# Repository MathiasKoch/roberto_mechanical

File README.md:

# Roberto the robot! Mechanical repository containing PCBs and mechanical drawing files.

Please see the roberto_robot repository for the actual robot software, issue tracker and wiki

https://github.com/smilykoch/roberto_robot

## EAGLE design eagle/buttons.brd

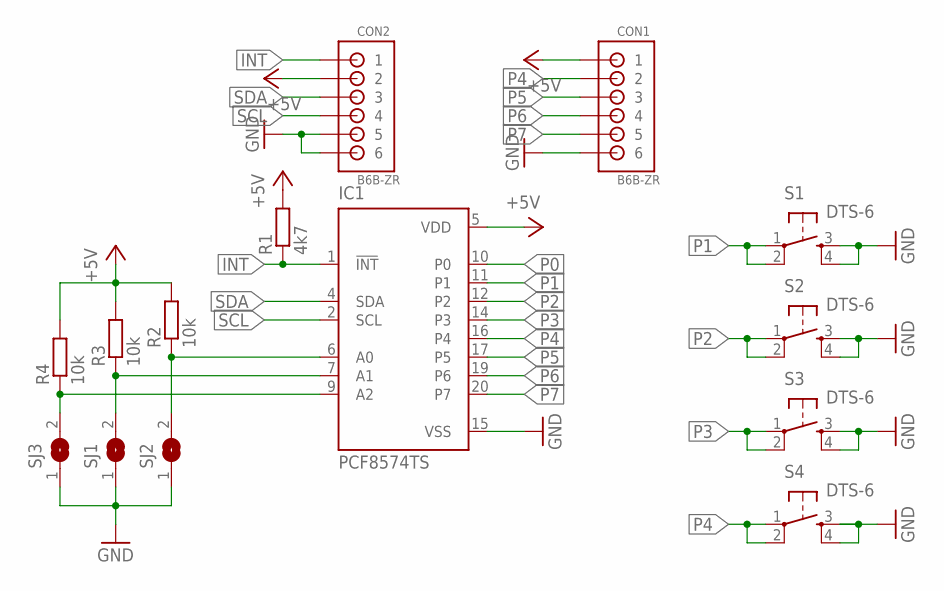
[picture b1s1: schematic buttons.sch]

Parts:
CON1, CON2: B6B-ZR
IC1: PCF8574TS; SSOP20
R1: 4k7; R0805
R2, R3, R4: 10k; R0805
S1, S2, S3, S4: DTS-6
SJ1, SJ2, SJ3: SJ

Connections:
+5V: CON1.1, CON2.2, IC1.5 (VDD), R1.2, R2.2, R3.2, R4.2
GND: CON1.6, CON2.5, CON2.6, IC1.15 (VSS), S1.3, S1.4, S2.3, S2.4, S3.3, S3.4, S4.3, S4.4, SJ1.1, SJ2.1, SJ3.1
INT: CON2.1, IC1.1 (!INT), R1.1
unnamed: IC1.6 (A0), R2.1, SJ2.2
unnamed: IC1.7 (A1), R3.1, SJ1.2
unnamed: IC1.9 (A2), R4.1, SJ3.2
P0: IC1.10 (P0)
P1: IC1.11 (P1), S1.1, S1.2
P2: IC1.12 (P2), S2.1, S2.2
P3: IC1.14 (P3), S3.1, S3.2
P4: CON1.2, IC1.16 (P4), S4.1, S4.2
P5: CON1.3, IC1.17 (P5)
P6: CON1.4, IC1.19 (P6)
P7: CON1.5, IC1.20 (P7)
SCL: CON2.4, IC1.2 (SCL)
SDA: CON2.3, IC1.4 (SDA)

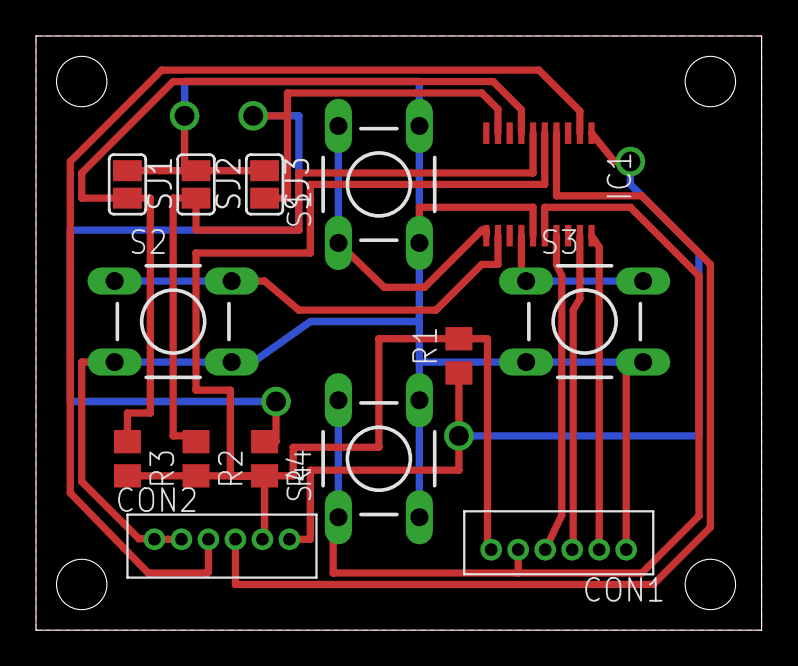
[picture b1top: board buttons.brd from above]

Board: 2 copper layers, 40.3 x 33.0 mm, 14 parts (0 on the bottom side), 15 nets.

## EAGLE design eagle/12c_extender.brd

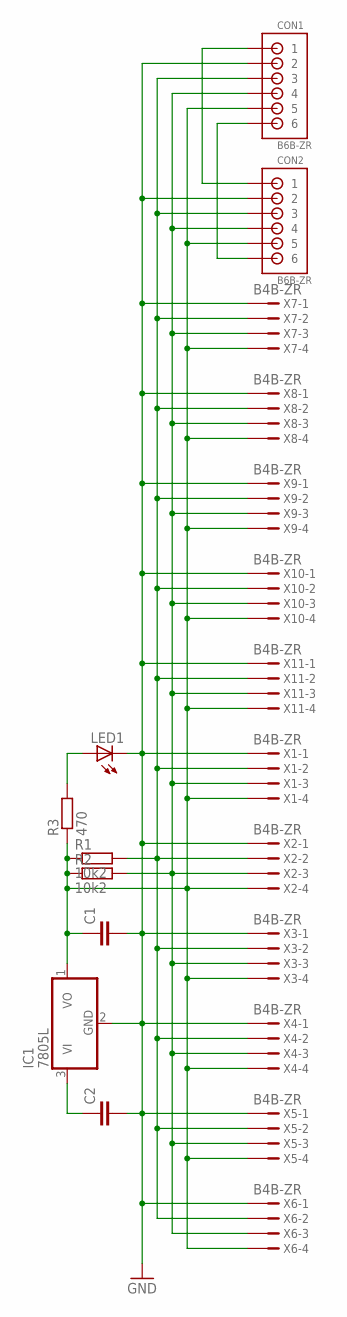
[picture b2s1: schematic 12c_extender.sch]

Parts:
C1, C2: C-EUC0805; C0805
CON1, CON2: B6B-ZR
IC1: 7805L; TO92
LED1: LEDSMT1206; 1206
R1, R2: 10k2; R0805
R3: 470; R0805
X1, X2, X3, X4, X5, X6, X7, X8, X9, X10, X11: B4B-ZR

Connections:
+5V: C1.1, CON1.5, CON2.5, IC1.1 (VO), R1.1, R2.1, R3.1, X1.4, X2.4, X3.4, X4.4, X5.4, X6.4, X7.4, X8.4, X9.4, X10.4, X11.4
GND: C1.2, C2.2, CON1.2, CON2.2, IC1.2 (GND), LED1.C, X1.1, X2.1, X3.1, X4.1, X5.1, X6.1, X7.1, X8.1, X9.1, X10.1, X11.1
unnamed: C2.1, IC1.3 (VI)
unnamed: LED1.A, R3.2
unnamed: CON1.1, CON2.1
unnamed: CON1.6, CON2.6
SCL: CON1.4, CON2.4, R2.2, X1.3, X2.3, X3.3, X4.3, X5.3, X6.3, X7.3, X8.3, X9.3, X10.3, X11.3
SDA: CON1.3, CON2.3, R1.2, X1.2, X2.2, X3.2, X4.2, X5.2, X6.2, X7.2, X8.2, X9.2, X10.2, X11.2

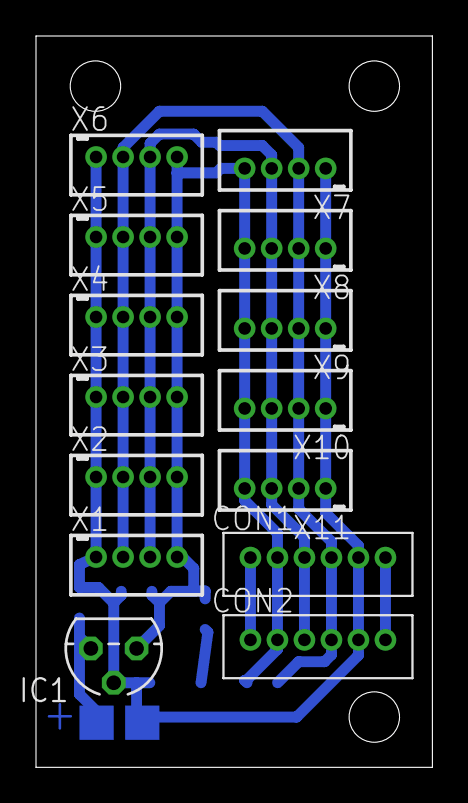
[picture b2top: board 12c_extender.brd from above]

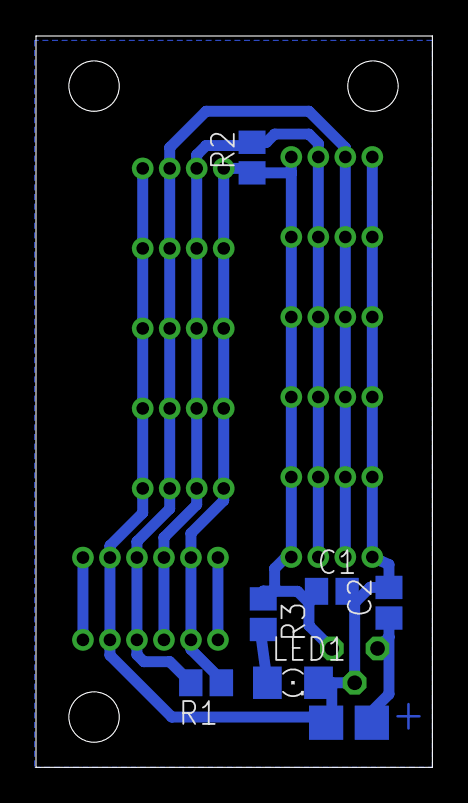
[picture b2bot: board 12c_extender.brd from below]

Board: 2 copper layers, 22.0 x 40.6 mm, 20 parts (6 on the bottom side), 8 nets.

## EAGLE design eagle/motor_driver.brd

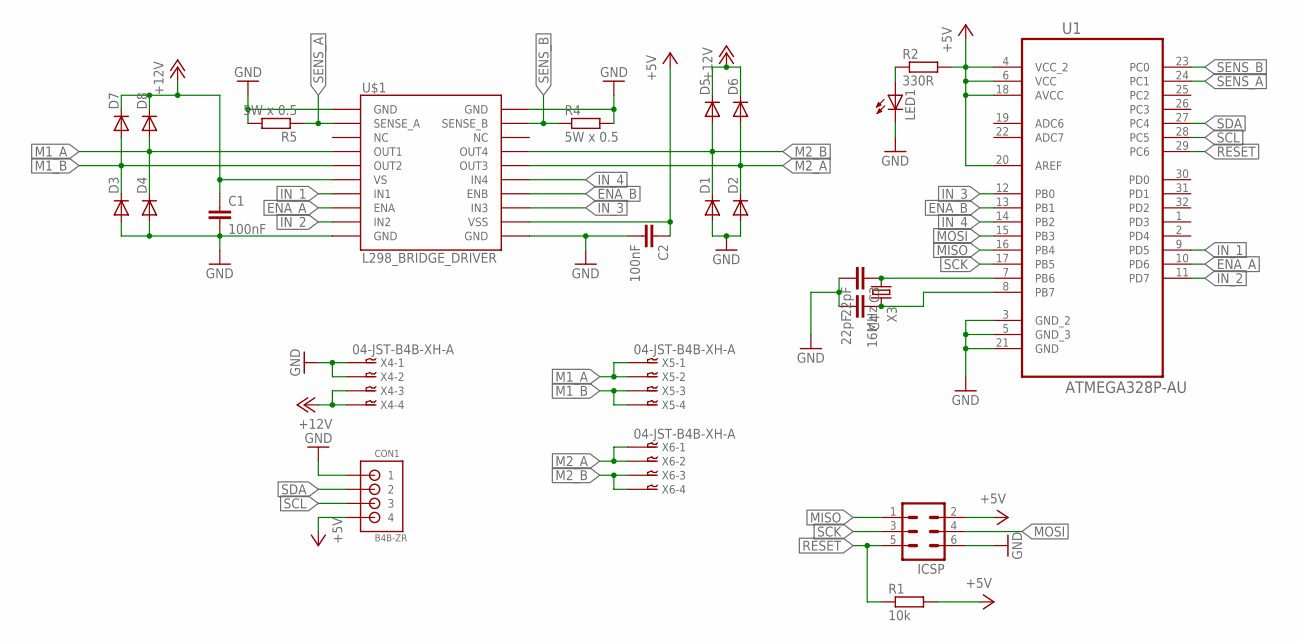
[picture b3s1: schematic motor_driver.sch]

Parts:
C1, C2: 100nF; C1206K
C3, C4: 22pF; C1206K
CON1: B4B-ZR
D1, D2, D3, D4, D5, D6, D7, D8: DIODE-SMC; SMC
ICSP: MA03-2
LED1: LEDCHIPLED_1206; CHIPLED_1206
R1: 10k; M3216
R2: 330R; M3216
R4, R5: 5W x 0.5; R6332
U1: ATMEGA328P-AU; QFP80P900X900X120-32N
U$1: L298_BRIDGE_DRIVER; POWERSO20
X3: 16MHz; 7.5X5-2-PAD
X4, X5, X6: 04-JST-B4B-XH-A; B4B-XH

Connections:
+5V: C2.1, CON1.4, ICSP.2, R1.2, R2.2, U1.4 (VCC_2), U1.6 (VCC), U1.18 (AVCC), U1.20 (AREF), U$1.12 (VSS)
+12V: C1.1, D5.C, D6.C, D7.C, D8.C, U$1.6 (VS), X4.P$3
ENA_A: U1.10 (PD6), U$1.8 (ENA)
ENA_B: U1.13 (PB1), U$1.14 (ENB)
GND: C1.2, C2.2, C3.2, C4.2, CON1.1, D1.A, D2.A, D3.A, D4.A, ICSP.6, LED1.C, R4.P$2 (2), R5.P$2 (2), U1.3 (GND_2), U1.5 (GND_3), U1.21 (GND), U$1.1 (GND), U$1.10 (GND), U$1.11 (GND), U$1.20 (GND), X4.P$2
IN_1: U1.9 (PD5), U$1.7 (IN1)
IN_2: U1.11 (PD7), U$1.9 (IN2)
IN_3: U1.12 (PB0), U$1.13 (IN3)
IN_4: U1.14 (PB2), U$1.15 (IN4)
M1_A: D4.C, D8.A, U$1.4 (OUT1), X5.P$1, X5.P$2
M1_B: D3.C, D7.A, U$1.5 (OUT2), X5.P$3, X5.P$4
M2_A: D2.C, D6.A, U$1.16 (OUT3), X6.P$1, X6.P$2
M2_B: D1.C, D5.A, U$1.17 (OUT4), X6.P$3, X6.P$4
MISO: ICSP.1, U1.16 (PB4)
MOSI: ICSP.4, U1.15 (PB3)
unnamed: LED1.A, R2.1
unnamed: C4.1, U1.8 (PB7), X3.2
unnamed: C3.1, U1.7 (PB6), X3.1
RESET: ICSP.5, R1.1, U1.29 (PC6)
SCK: ICSP.3, U1.17 (PB5)
SCL: CON1.3, U1.28 (PC5)
SDA: CON1.2, U1.27 (PC4)
SENS_A: R5.P$1 (1), U1.24 (PC1), U$1.2 (SENSE_A)
SENS_B: R4.P$1 (1), U1.23 (PC0), U$1.19 (SENSE_B)

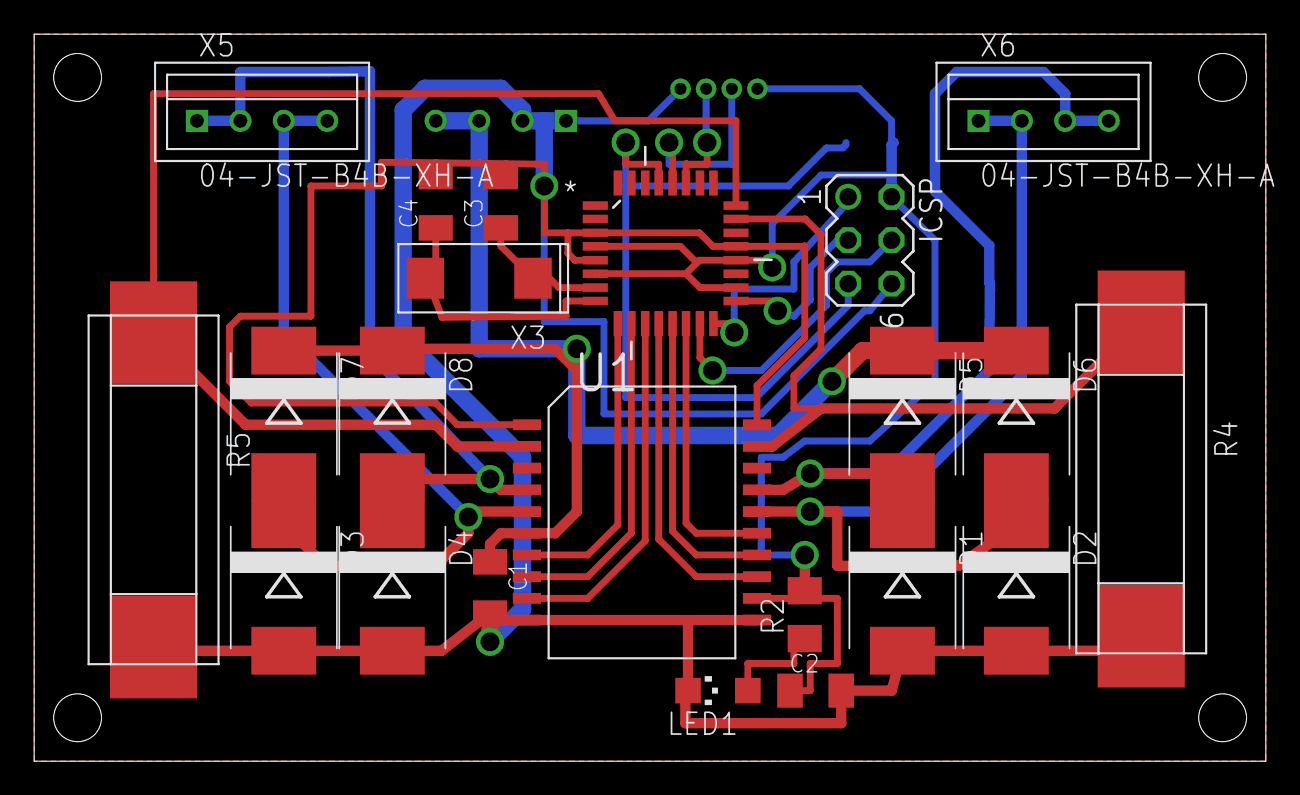
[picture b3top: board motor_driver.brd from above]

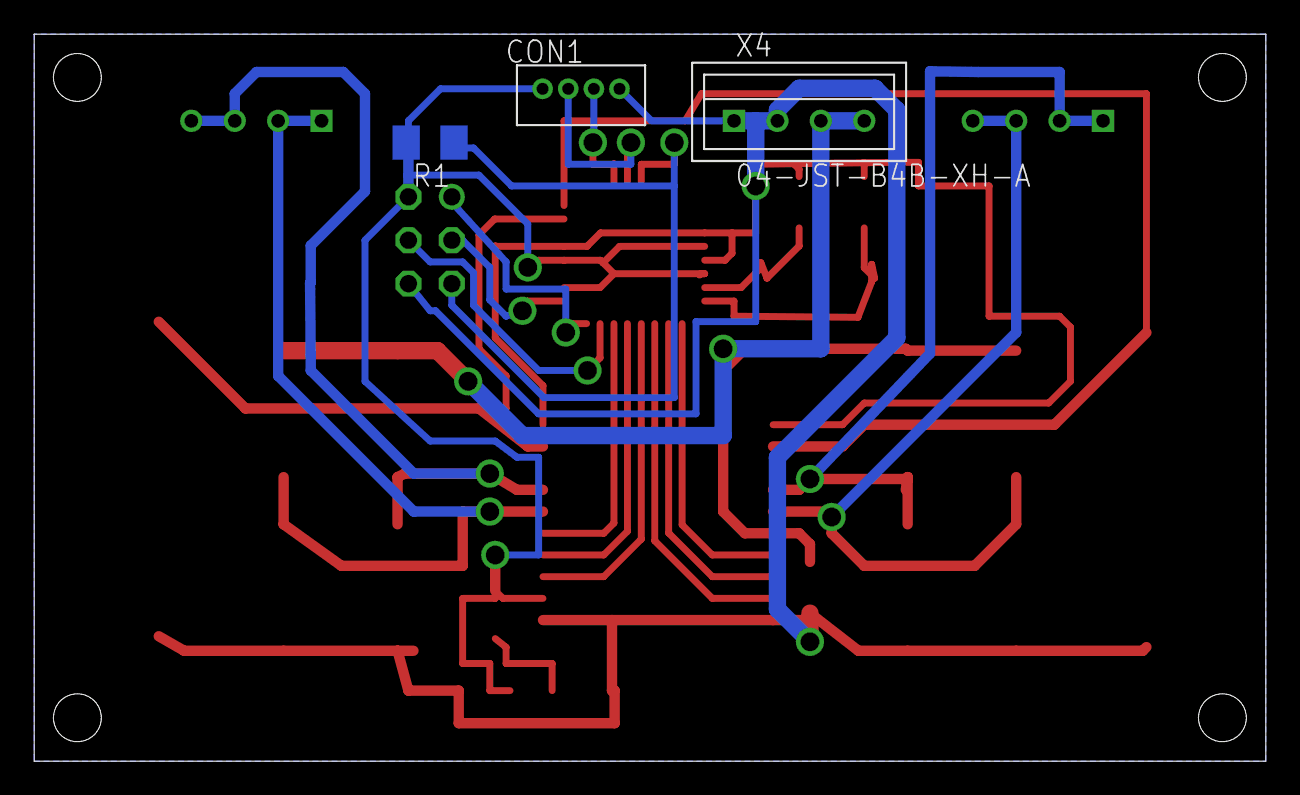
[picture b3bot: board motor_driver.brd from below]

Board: 2 copper layers, 72.1 x 42.5 mm, 25 parts (3 on the bottom side), 24 nets.

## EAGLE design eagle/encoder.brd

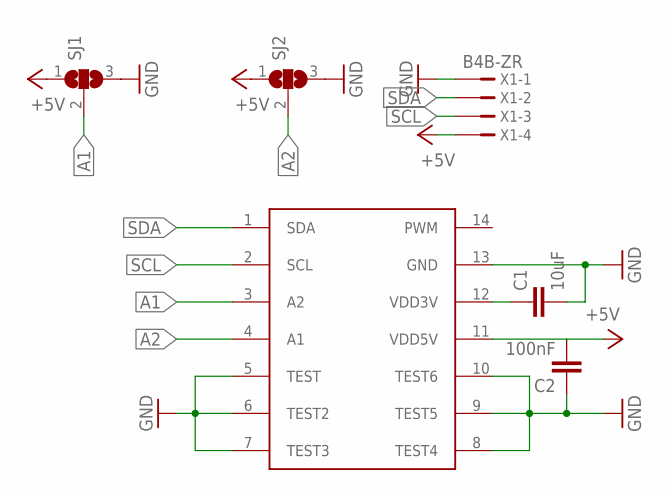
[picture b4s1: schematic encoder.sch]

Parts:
C1: 10uF; C0805K
C2: 100nF; C0805K
SJ1, SJ2: SJ2W; SJ_2
U$1: AS5048B; TSSOP14
X1: B4B-ZR

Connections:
+5V: C2.2, SJ1.1, SJ2.1, U$1.11 (VDD5V), X1.4
A1: SJ1.2, U$1.3 (A2)
A2: SJ2.2, U$1.4 (A1)
GND: C1.2, C2.1, SJ1.3, SJ2.3, U$1.5 (TEST), U$1.6 (TEST2), U$1.7 (TEST3), U$1.8 (TEST4), U$1.9 (TEST5), U$1.10 (TEST6), U$1.13 (GND), X1.1
unnamed: C1.1, U$1.12 (VDD3V)
SCL: U$1.2 (SCL), X1.3
SDA: U$1.1 (SDA), X1.2

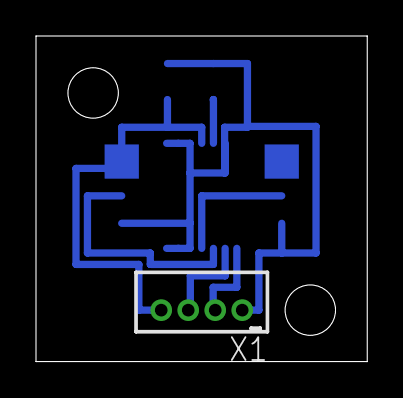
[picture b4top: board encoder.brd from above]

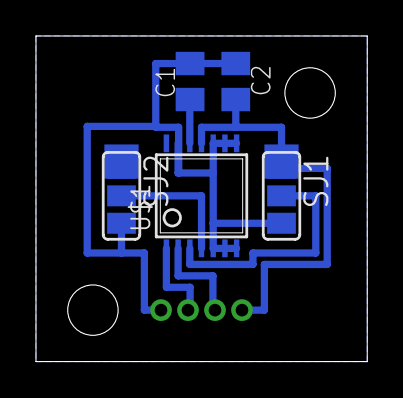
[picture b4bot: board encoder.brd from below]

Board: 2 copper layers, 18.4 x 18.1 mm, 6 parts (5 on the bottom side), 7 nets.

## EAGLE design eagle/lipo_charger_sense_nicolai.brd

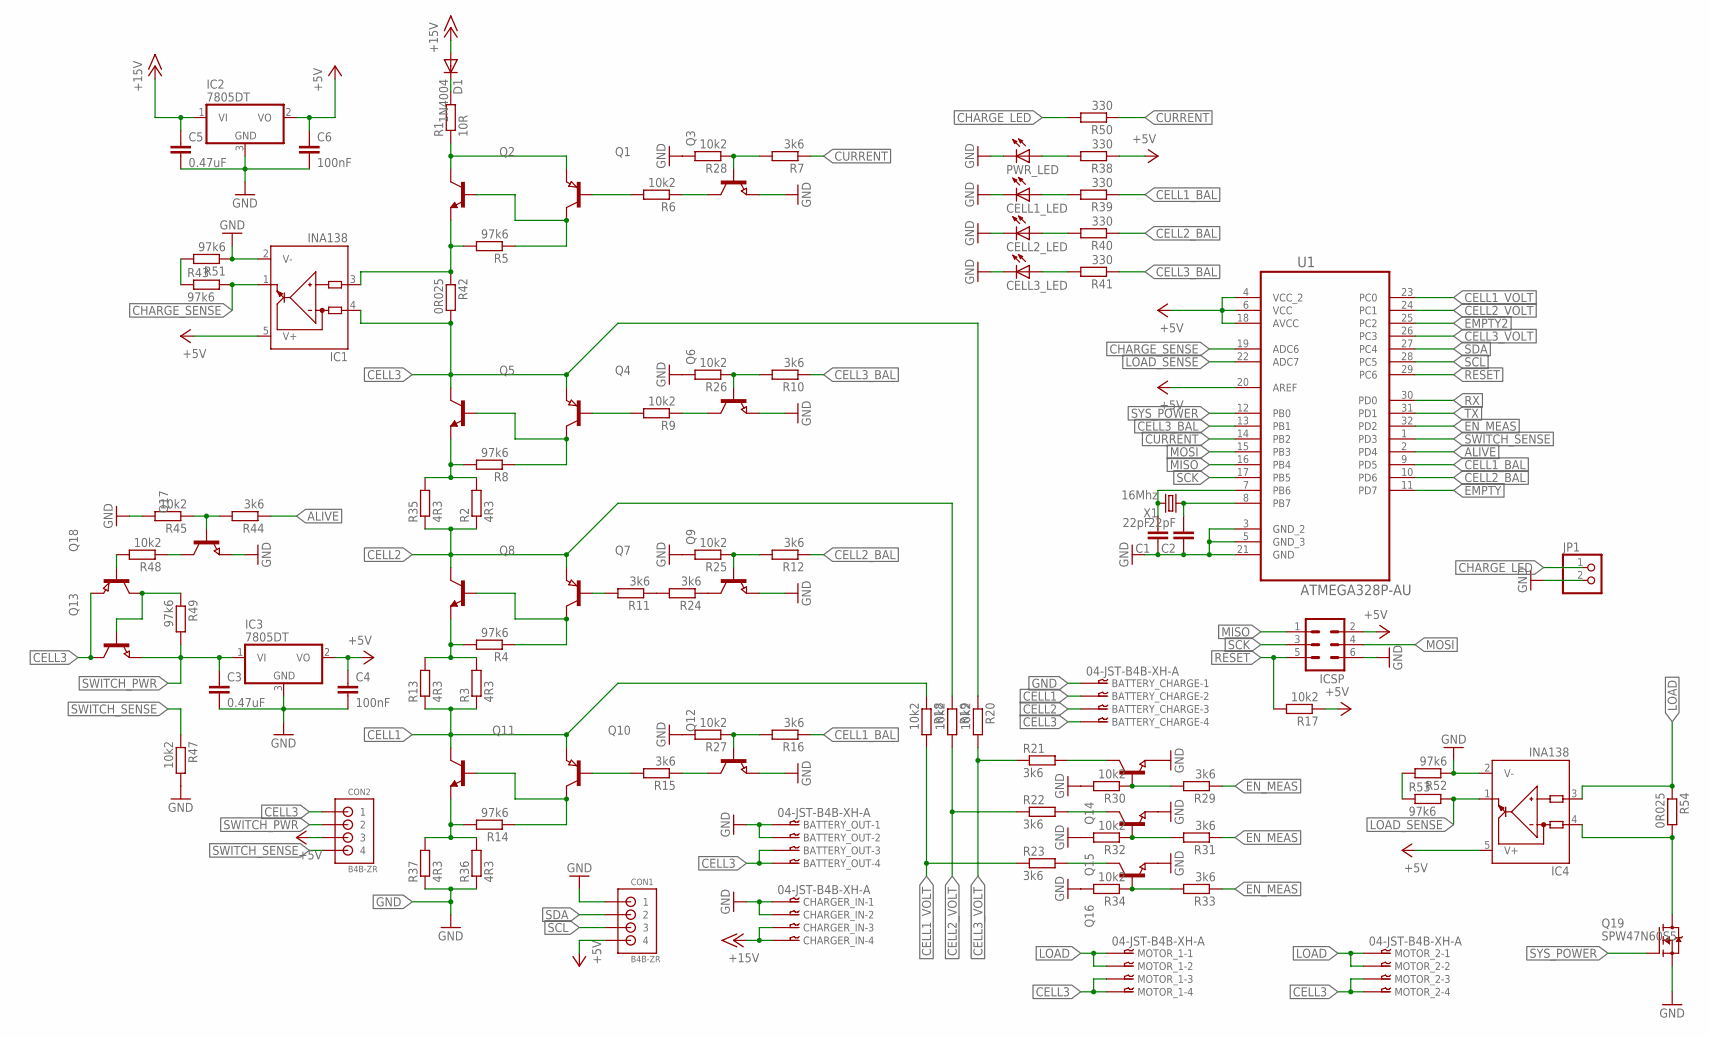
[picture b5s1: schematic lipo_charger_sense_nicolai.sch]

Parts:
BATTERY_CHARGE: 04-JST-B4B-XH-A; B4B-XH
BATTERY_OUT: 04-JST-B4B-XH-A; B4B-XH
C1, C2: 22pF; C0805K
C3, C5: 0.47uF; C0805K
C4, C6: 100nF; C0805K
CELL1_LED, CELL2_LED, CELL3_LED: LEDSMT1206; 1206
CHARGER_IN: 04-JST-B4B-XH-A; B4B-XH
CON1, CON2: B4B-ZR
D1: 1N4004; DO41-10
IC1, IC4: INA138; SOT23-5
IC2, IC3: 7805DT; TO252
ICSP: MA03-2
JP1: PINHD-1X2/90; 1X02/90
MOTOR_1, MOTOR_2: 04-JST-B4B-XH-A; B4B-XH
PWR_LED: LEDSMT1206; 1206
Q1, Q4, Q7, Q10, Q18: PNP-TRANSISTOR_SOT23; SOT23
Q2, Q5, Q8, Q11: -NPN-; DPAK
Q3, Q6, Q9, Q12, Q13, Q14, Q15, Q16, Q17: NPN-TRANSISTOR_SOT23; SOT23
Q19: SPW47N60S5; DPACK_2
R1: 10R; SMW5
R2, R3, R13, R35, R36, R37: 4R3; SMW5
R4, R5, R8, R14, R43, R49, R51, R52, R53: 97k6; R0805
R6, R9, R17, R18, R19, R20, R25, R26, R27, R28, R30, R32, R34, R45, R47, R48: 10k2; R0805
R7, R10, R11, R12, R15, R16, R21, R22, R23, R24, R29, R31, R33, R44: 3k6; R0805
R38, R39, R40, R41, R50: 330; R0805
R42, R54: 0R025; R2512
U1: ATMEGA328P-AU; QFP80P900X900X120-32N
X1: 16Mhz; 7.5X5-2-PAD

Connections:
+5V: C4.1, C6.1, CON1.4, CON2.3, IC1.5 (V+), IC2.2 (VO), IC3.2 (VO), IC4.5 (V+), ICSP.2, R17.1, R38.1, U1.4 (VCC_2), U1.6 (VCC), U1.18 (AVCC), U1.20 (AREF)
+15V: C5.1, CHARGER_IN.P$3, CHARGER_IN.P$4, D1.A, IC2.1 (VI)
ALIVE: R44.1, U1.2 (PD4)
CELL1: BATTERY_CHARGE.P$2, Q10.2 (E), Q11.3 (C), R3.P$1 (1), R13.P$1 (1), R18.1
CELL1_BAL: R16.1, R39.1, U1.9 (PD5)
CELL1_VOLT: R18.2, R23.1, U1.23 (PC0)
CELL2: BATTERY_CHARGE.P$3, Q7.2 (E), Q8.3 (C), R2.P$1 (1), R19.1, R35.P$1 (1)
CELL2_BAL: R12.1, R40.1, U1.10 (PD6)
CELL2_VOLT: R19.2, R22.1, U1.24 (PC1)
CELL3: BATTERY_CHARGE.P$4, BATTERY_OUT.P$3, BATTERY_OUT.P$4, CON2.1, IC1.4 (IN-), MOTOR_1.P$3, MOTOR_1.P$4, MOTOR_2.P$3, MOTOR_2.P$4, Q4.2 (E), Q5.3 (C), Q13.3 (C), Q18.2 (E), R20.1, R42.2
CELL3_BAL: R10.1, R41.1, U1.13 (PB1)
CELL3_VOLT: R20.2, R21.1, U1.26 (PC3)
CELL5: IC4.4 (IN-), Q19.D, R54.2
CHARGE_LED: JP1.1, R50.2
CHARGE_SENSE: IC1.1 (OUT), R43.2, U1.19 (ADC6)
CURRENT: R7.1, R50.1, U1.14 (PB2)
EMPTY: U1.11 (PD7)
EMPTY2: U1.25 (PC2)
EN_MEAS: R29.1, R31.1, R33.1, U1.32 (PD2)
GND: BATTERY_CHARGE.P$1, BATTERY_OUT.P$1, BATTERY_OUT.P$2, C1.1, C2.1, C3.2, C4.2, C5.2, C6.2, CELL1_LED.C, CELL2_LED.C, CELL3_LED.C, CHARGER_IN.P$1, CHARGER_IN.P$2, CON1.1, IC1.2 (V-), IC2.3 (GND), IC3.3 (GND), IC4.2 (V-), ICSP.6, JP1.2, PWR_LED.C, Q3.2 (E), Q6.2 (E), Q9.2 (E), Q12.2 (E), Q14.2 (E), Q15.2 (E), Q16.2 (E), Q17.2 (E), Q19.S, R25.2, R26.2, R27.2, R28.2, R30.2, R32.2, R34.2, R36.P$1 (1), R37.P$1 (1), R45.2, R47.2, R51.1, R52.1, U1.3 (GND_2), U1.5 (GND_3), U1.21 (GND)
LOAD: IC4.3 (IN+), MOTOR_1.P$1, MOTOR_1.P$2, MOTOR_2.P$1, MOTOR_2.P$2, R54.1
LOAD_SENSE: IC4.1 (OUT), R53.2, U1.22 (ADC7)
MISO: ICSP.1, U1.16 (PB4)
MOSI: ICSP.4, U1.15 (PB3)
unnamed: Q1.1 (B), R6.2
unnamed: Q1.3 (C), Q2.1 (B), R5.1
unnamed: Q1.2 (E), Q2.3 (C), R1.P$1 (1)
unnamed: Q7.1 (B), R11.2
unnamed: Q7.3 (C), Q8.1 (B), R4.1
unnamed: Q3.3 (C), R6.1
unnamed: Q3.1 (B), R7.2, R28.1
unnamed: Q4.1 (B), R9.2
unnamed: Q4.3 (C), Q5.1 (B), R8.1
unnamed: C2.2, U1.8 (PB7), X1.1
unnamed: Q5.4 (E), R2.P$2 (2), R8.2, R35.P$2 (2)
unnamed: Q6.3 (C), R9.1
unnamed: Q6.1 (B), R10.2, R26.1
unnamed: R11.1, R24.2
unnamed: Q8.4 (E), R3.P$2 (2), R4.2, R13.P$2 (2)
unnamed: Q9.3 (C), R24.1
unnamed: Q9.1 (B), R12.2, R25.1
unnamed: Q10.1 (B), R15.2
unnamed: Q10.3 (C), Q11.1 (B), R14.1
unnamed: Q16.3 (C), R23.2
unnamed: Q11.4 (E), R14.2, R36.P$2 (2), R37.P$2 (2)
unnamed: Q12.3 (C), R15.1
unnamed: Q12.1 (B), R16.2, R27.1
unnamed: Q15.3 (C), R22.2
unnamed: Q14.3 (C), R21.2
unnamed: PWR_LED.A, R38.2
unnamed: Q14.1 (B), R29.2, R30.1
unnamed: CELL1_LED.A, R39.2
unnamed: Q15.1 (B), R31.2, R32.1
unnamed: CELL2_LED.A, R40.2
unnamed: CELL3_LED.A, R41.2
unnamed: Q16.1 (B), R33.2, R34.1
unnamed: IC1.3 (IN+), Q2.4 (E), R5.2, R42.1
unnamed: D1.C, R1.P$2 (2)
unnamed: Q17.1 (B), R44.2, R45.1
unnamed: Q13.1 (B), Q18.3 (C), R49.1
unnamed: R43.1, R51.2
unnamed: Q18.1 (B), R48.2
unnamed: Q17.3 (C), R48.1
unnamed: R52.2, R53.1
PB6: C1.2, U1.7 (PB6), X1.2
RESET: ICSP.5, R17.2, U1.29 (PC6)
RX: U1.30 (PD0)
SCK: ICSP.3, U1.17 (PB5)
SCL: CON1.3, U1.28 (PC5)
SDA: CON1.2, U1.27 (PC4)
SWITCH_PWR: C3.1, CON2.2, IC3.1 (VI), Q13.2 (E), R49.2
SWITCH_SENSE: CON2.4, R47.1, U1.1 (PD3)
SYS_POWER: Q19.G, U1.12 (PB0)
TX: U1.31 (PD1)

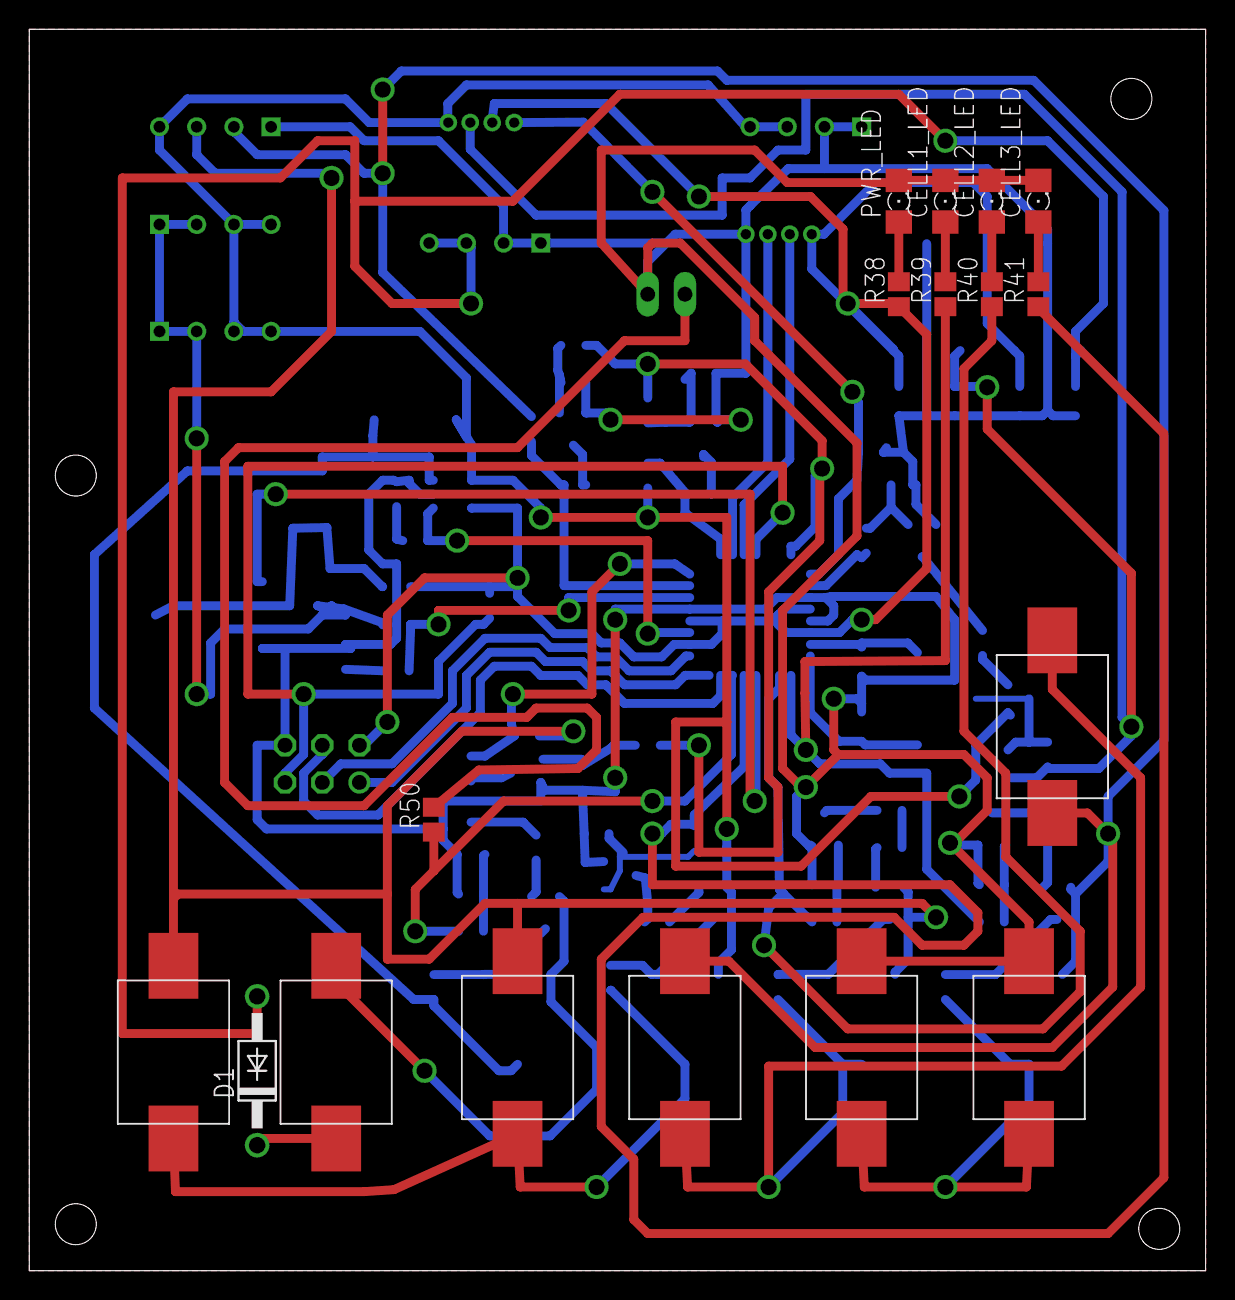
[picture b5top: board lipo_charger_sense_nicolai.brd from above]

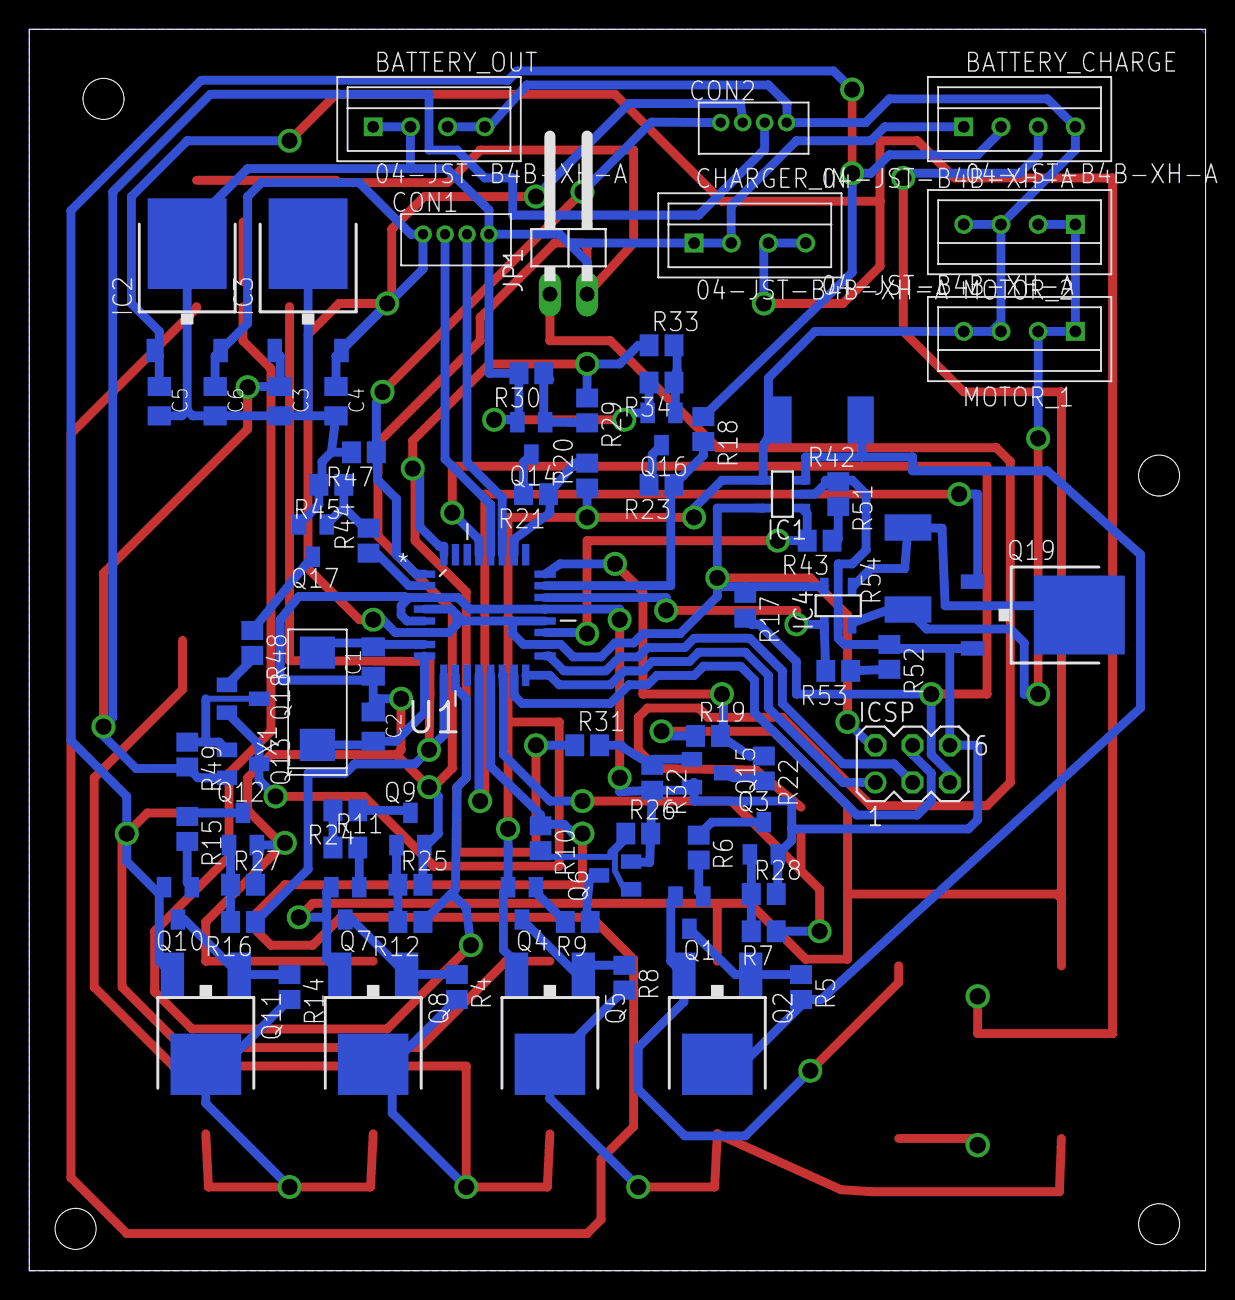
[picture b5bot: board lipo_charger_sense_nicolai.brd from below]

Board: 2 copper layers, 80.3 x 84.8 mm, 98 parts (81 on the bottom side), 70 nets.

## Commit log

2016-10-30 Initial commit of all mechanical files, in the process of moving from dropbox to github
2016-11-07 Fixed gears for mechanical model
2016-11-07 Changed README
2016-11-09 Added first two detailed PCBs to model
2016-11-10 Added all the detailed PCBs to the model, and added the CircuitWorks component library for recreation purposes
2016-11-17 Changed center gear cylinder and added 20mm standoffs between Odroid and camera mount
2016-11-17 Added display assembly
2017-02-08 Added version 4 charger schematics, and other parts
2017-02-12 Just ordered charger_v4 and distribution_v2
2017-08-20 Commit at time of ordering PCBs, Motor_v5, Charger_v5 and Distribution_v3
2021-03-21 Add distribution v3

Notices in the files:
parts and their libraries:
SparkFun-PowerIC: Licensing: Creative Commons ShareAlike 4.0 International - https://creativecommons.org/licenses/by-sa/4.0
